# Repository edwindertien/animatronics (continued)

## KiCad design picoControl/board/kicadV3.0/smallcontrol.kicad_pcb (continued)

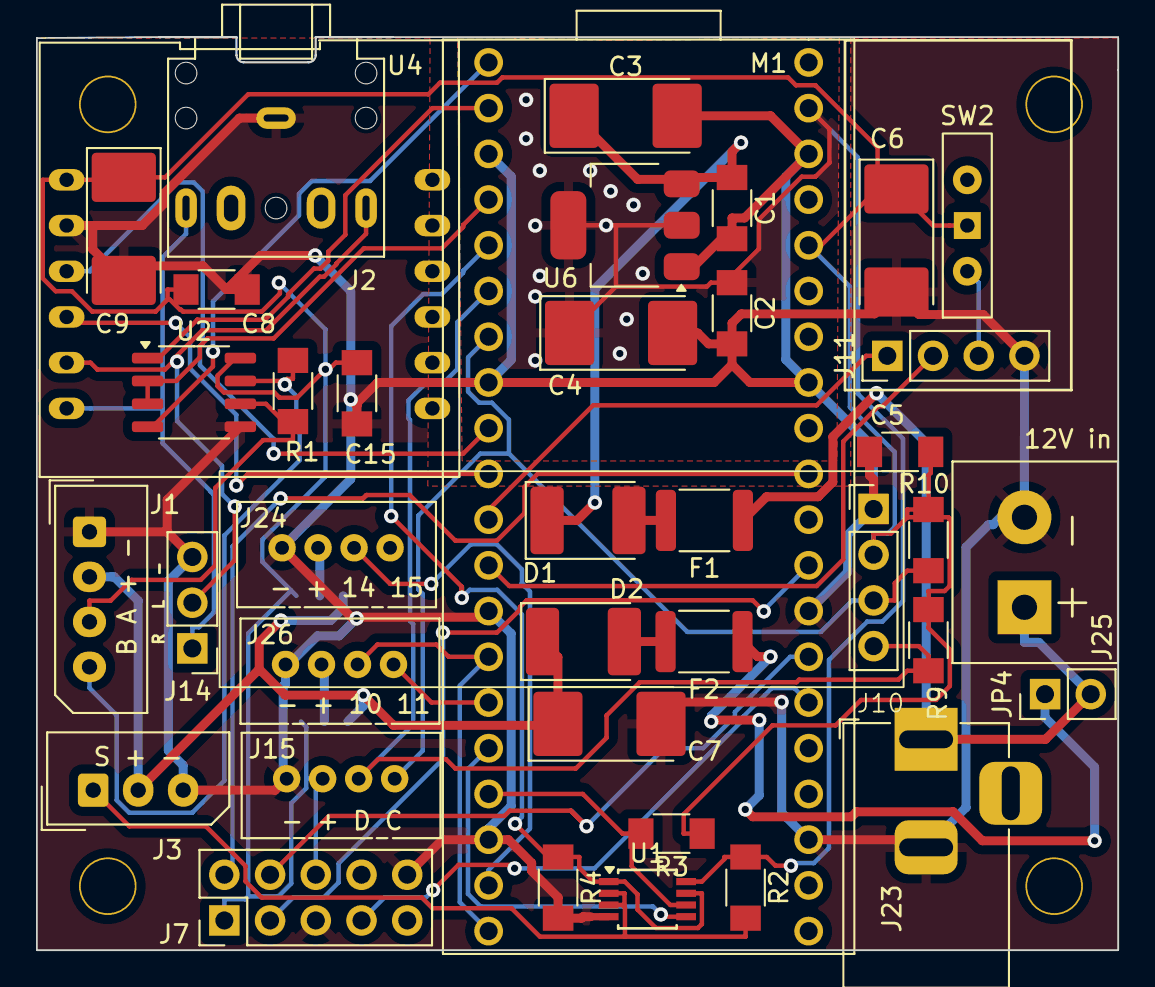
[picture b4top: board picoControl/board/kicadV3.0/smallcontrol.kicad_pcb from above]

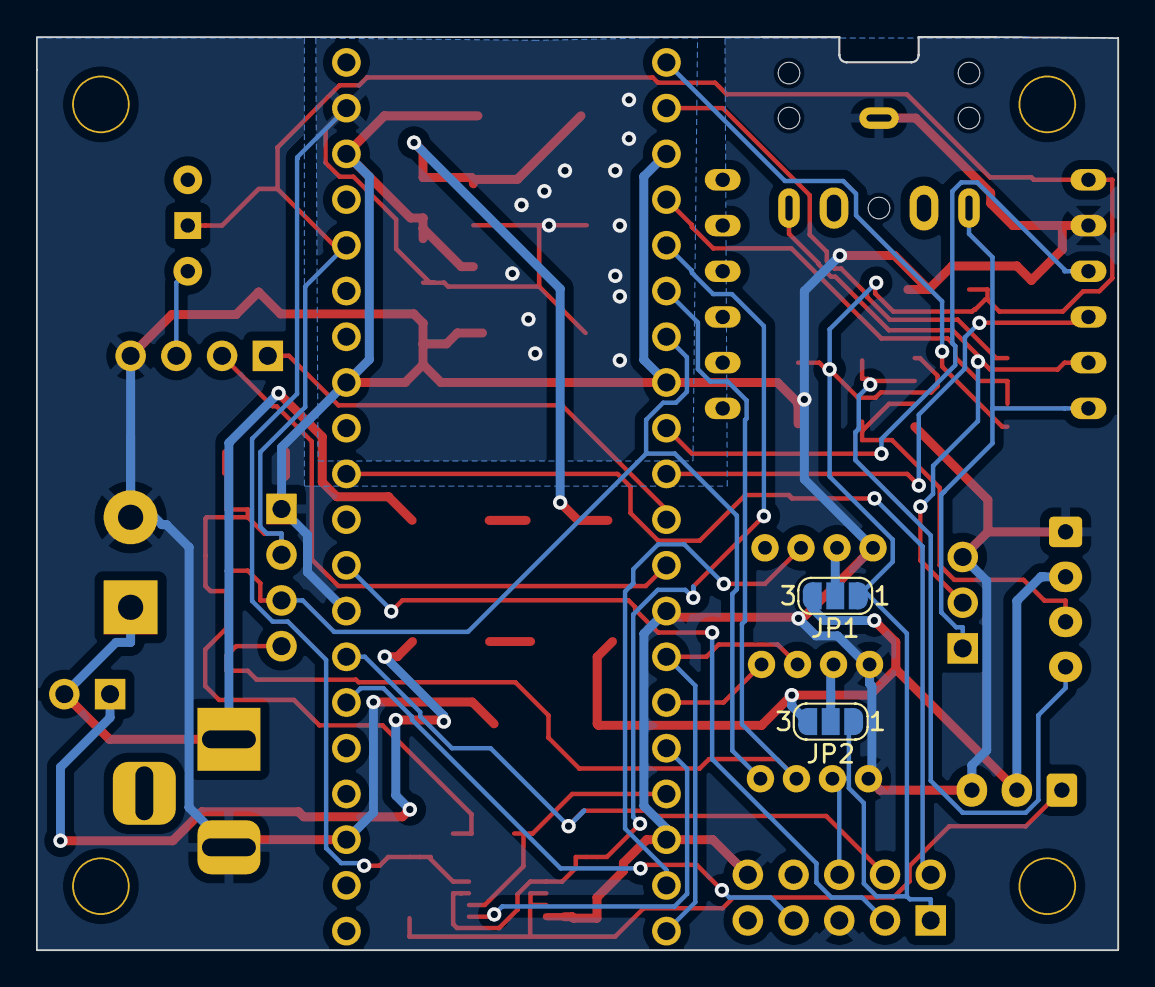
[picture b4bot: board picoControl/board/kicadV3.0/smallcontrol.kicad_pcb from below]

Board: 2 copper layers, 60.1 x 50.7 mm, 45 parts (2 on the bottom side), 36 nets.

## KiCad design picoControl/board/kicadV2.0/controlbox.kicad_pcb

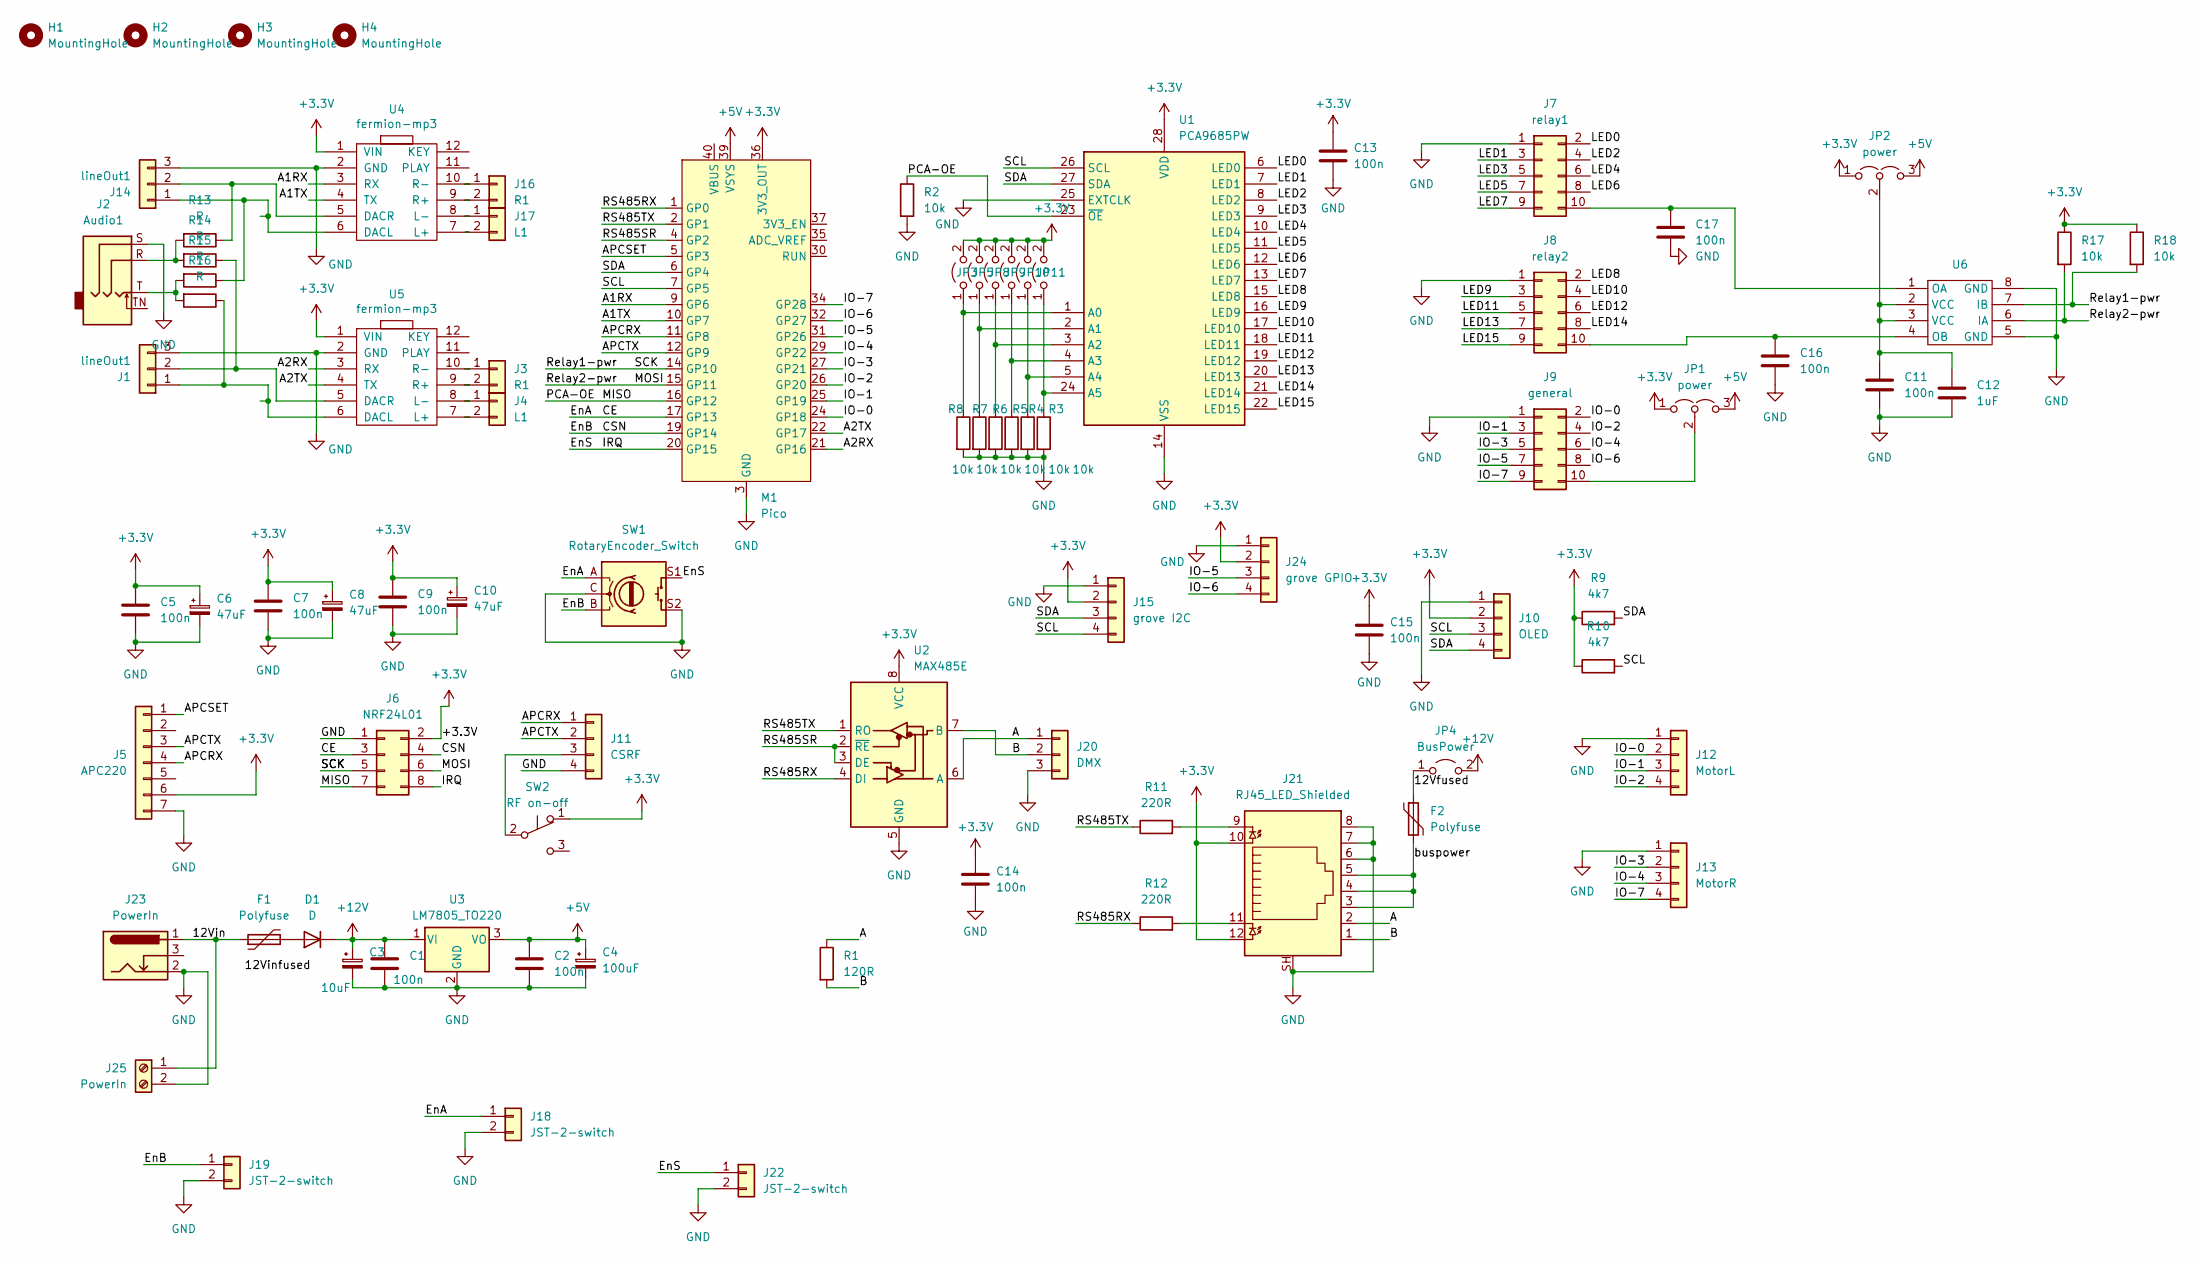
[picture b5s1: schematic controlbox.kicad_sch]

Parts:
C1, C2, C5, C7, C9, C11, C13, C14, C15, C16, C17: 100n; C_1206
C3: 10uF; CP_Elec_D6.3mm_H6.1mm
C4: 100uF; CP_Elec_D6.3mm_H6.1mm
C6, C8, C10: 47uF; CP_Elec_D6.3mm_H6.1mm
C12: 1uF; C_1206
D1: D; D_2512_6332Metric_Pad1.52x3.35mm_HandSolder
F1, F2: Polyfuse; Fuse_2920_7451Metric
H1, H2, H3, H4: MountingHole; MountingHole_3mm
J1, J14: lineOut1; PinHeader_1x03_P2.54mm_Vertical
J2: Audio1; Jack_3.5mm_CUI_SJ1-3525N_Horizontal
J3, J16: R1; JST_XH_B2B-XH-A_1x02_P2.50mm_Vertical
J4, J17: L1; JST_XH_B2B-XH-A_1x02_P2.50mm_Vertical
J5: APC220
J6: NRF24L01; PinHeader_2x04_P2.54mm_Vertical
J7: relay1; IDC-Header_2x05_P2.54mm_Vertical
J8: relay2; IDC-Header_2x05_P2.54mm_Vertical
J9: general; IDC-Header_2x05_P2.54mm_Vertical
J10: OLED; OLED128x32
J11: CSRF; PinHeader_1x04_P2.54mm_Vertical
J12: MotorL; JST_XH_B4B-XH-A_1x04_P2.50mm_Vertical
J13: MotorR; JST_XH_B4B-XH-A_1x04_P2.50mm_Vertical
J15: grove I2C; Grove_1x04
J18, J19, J22: JST-2-switch; JST_XH_B2B-XH-A_1x02_P2.50mm_Vertical
J20: DMX; JST_XH_B3B-XH-A_1x03_P2.50mm_Vertical
J21: RJ45_LED_Shielded; RJ45_Amphenol_RJHSE538X
J23: PowerIn; BarrelJack_Horizontal
J24: grove GPIO; Grove_1x04
J25: PowerIn; TerminalBlock_OnShore_1x02_P5.00mm_Horizontal
JP1, JP2: power; PinHeader_1x03_P2.54mm_Vertical
JP3, JP5, JP8, JP9, JP10, JP11: Jumper_2_Open; SolderJumper-2_P1.3mm_Open_RoundedPad1.0x1.5mm
JP4: BusPower; PinHeader_1x02_P2.54mm_Vertical
M1: Pico; RaspberryPi_PicoW_SocketTHT
R1: 120R; R_1206
R2, R3, R4, R5, R6, R7, R8, R17, R18: 10k; R_1206
R9, R10: 4k7; R_1206
R11, R12: 220R; R_1206
R13, R14, R15, R16: R; R_1206
SW1: RotaryEncoder_Switch; RotaryEncoder_Alps_EC11E-Switch_Vertical_H20mm
SW2: RF on-off; SW_Slide_1P2T_CK_OS102011MS2Q
U1: PCA9685PW; TSSOP-28_4.4x9.7mm_P0.65mm
U2: MAX485E; SO-8_3.9x4.9mm_P1.27mm
U3: LM7805_TO220; TO-220-3_Vertical
U4, U5: fermion-mp3
U6: SO-8_3.9x4.9mm_P1.27mm

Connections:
+3.3V: C5.1, C6.1, C7.1, C8.1, C9.1, C10.1, C13.1, C14.1, C15.1, J5.6, J6.2, J10.2, J15.2, J21.10, J21.12, J24.2, JP1.1 (A), JP2.1 (A), JP3.2 (B), JP5.2 (B), JP8.2 (B), JP9.2 (B), JP10.2 (B), JP11.2 (B), M1.36 (3V3_OUT), R9.1, R10.1, R17.1, R18.1, SW2.1 (A), U1.28 (VDD), U2.8 (VCC), U4.1 (VIN), U5.1 (VIN)
+5V: C2.1, C4.1, JP1.3 (B), JP2.3 (B), M1.39 (VSYS), U3.3 (VO)
+12V: C1.1, C3.1, D1.1 (K), JP4.2 (B), U3.1 (VI)
/12Vfused: F2.1, JP4.1 (A)
/12Vin: F1.1, J23.1, J25.1
/A: J20.1, J21.2, R1.1, U2.6 (A)
/A1RX: M1.9 (GP6), U4.3 (RX)
/A1TX: M1.10 (GP7), U4.4 (TX)
/A2RX: M1.21 (GP16), U5.3 (RX)
/A2TX: M1.22 (GP17), U5.4 (TX)
/APCRX: J5.4, J11.1, M1.11 (GP8)
/APCSET: J5.1, M1.5 (GP3)
/APCTX: J5.3, J11.2, M1.12 (GP9)
/B: J20.2, J21.1, R1.2, U2.7 (B)
/CE: J6.3, J18.1, M1.17 (GP13), SW1.A
/CSN: J6.4, J19.1, M1.19 (GP14), SW1.B
/EnS: J6.8, J22.1, M1.20 (GP15), SW1.S1
/IO-0: J9.2, J12.2, M1.24 (GP18)
/IO-1: J9.3, J12.3, M1.25 (GP19)
/IO-2: J9.4, J12.4, M1.26 (GP20)
/IO-3: J9.5, J13.2, M1.27 (GP21)
/IO-4: J9.6, J13.3, M1.29 (GP22)
/IO-5: J9.7, J24.3, M1.31 (GP26)
/IO-6: J9.8, J24.4, M1.32 (GP27)
/IO-7: J9.9, J13.4, M1.34 (GP28)
/LED0: J7.2, U1.6 (LED0)
/LED1: J7.3, U1.7 (LED1)
/LED2: J7.4, U1.8 (LED2)
/LED3: J7.5, U1.9 (LED3)
/LED4: J7.6, U1.10 (LED4)
/LED5: J7.7, U1.11 (LED5)
/LED6: J7.8, U1.12 (LED6)
/LED7: J7.9, U1.13 (LED7)
/LED8: J8.2, U1.15 (LED8)
/LED9: J8.3, U1.16 (LED9)
/LED10: J8.4, U1.17 (LED10)
/LED11: J8.5, U1.18 (LED11)
/LED12: J8.6, U1.19 (LED12)
/LED13: J8.7, U1.20 (LED13)
/LED14: J8.8, U1.21 (LED14)
/LED15: J8.9, U1.22 (LED15)
/MISO: J6.7, M1.16 (GP12), R2.1, U1.23 (~OE)
/MOSI: J6.6, M1.15 (GP11), R17.2, U6.6 (IA)
/RS485RX: M1.1 (GP0), R12.1, U2.4 (DI)
/RS485SR: M1.4 (GP2), U2.2 (~RE), U2.3 (DE)
/RS485TX: M1.2 (GP1), R11.1, U2.1 (RO)
/Relay1-pwr: J6.5, M1.14 (GP10), R18.2, U6.7 (IB)
/SCL: J10.3, J15.4, M1.7 (GP5), R10.2, U1.26 (SCL)
/SDA: J10.4, J15.3, M1.6 (GP4), R9.2, U1.27 (SDA)
/buspower: F2.2, J21.3, J21.4, J21.5
GND: C1.2, C2.2, C3.2, C4.2, C5.2, C6.2, C7.2, C8.2, C9.2, C10.2, C11.2, C12.2, C13.2, C14.2, C15.2, C16.2, C17.2, J1.3, J2.S, J5.7, J6.1, J7.1, J8.1, J9.1, J10.1, J11.4, J12.1, J13.1, J14.3, J15.1, J18.2, J19.2, J20.3, J21.6, J21.7, J21.8, J21.SH, J22.2, J23.2, J24.1, J25.2, M1.3 (GND), M1.8 (GND), M1.13 (GND), M1.18 (GND), M1.23 (GND), M1.28 (GND), M1.33 (GND), M1.38 (GND), R2.2, R3.2, R4.2, R5.2, R6.2, R7.2, R8.2, SW1.C, SW1.S2, U1.14 (VSS), U1.25 (EXTCLK), U2.5 (GND), U3.2 (GND), U4.2 (GND), U5.2 (GND), U6.5 (GND), U6.8 (GND)
unnamed: D1.2 (A), F1.2
unnamed: J1.1, R16.1, U5.6 (DACL)
unnamed: J1.2, R14.1, U5.5 (DACR)
unnamed: J2.R, R13.2, R14.2
unnamed: J2.T, R15.2, R16.2
unnamed: J3.1, U5.10 (R-)
unnamed: J3.2, U5.9 (R+)
unnamed: J4.1, U5.8 (L-)
unnamed: J4.2, U5.7 (L+)
unnamed: C17.1, J7.10, U6.1 (OA)
unnamed: C16.1, J8.10, U6.4 (OB)
unnamed: J9.10, JP1.2 (C)
unnamed: J11.3, SW2.2 (B)
unnamed: J14.1, R15.1, U4.6 (DACL)
unnamed: J14.2, R13.1, U4.5 (DACR)
unnamed: J16.1, U4.10 (R-)
unnamed: J16.2, U4.9 (R+)
unnamed: J17.1, U4.8 (L-)
unnamed: J17.2, U4.7 (L+)
unnamed: J21.9, R11.2
unnamed: J21.11, R12.2
unnamed: C11.1, C12.1, JP2.2 (C), U6.2 (VCC), U6.3 (VCC)
unnamed: JP3.1 (A), R8.1, U1.1 (A0)
unnamed: JP5.1 (A), R7.1, U1.2 (A1)
unnamed: JP8.1 (A), R6.1, U1.3 (A2)
unnamed: JP9.1 (A), R5.1, U1.4 (A3)
unnamed: JP10.1 (A), R4.1, U1.5 (A4)
unnamed: JP11.1 (A), R3.1, U1.24 (A5)

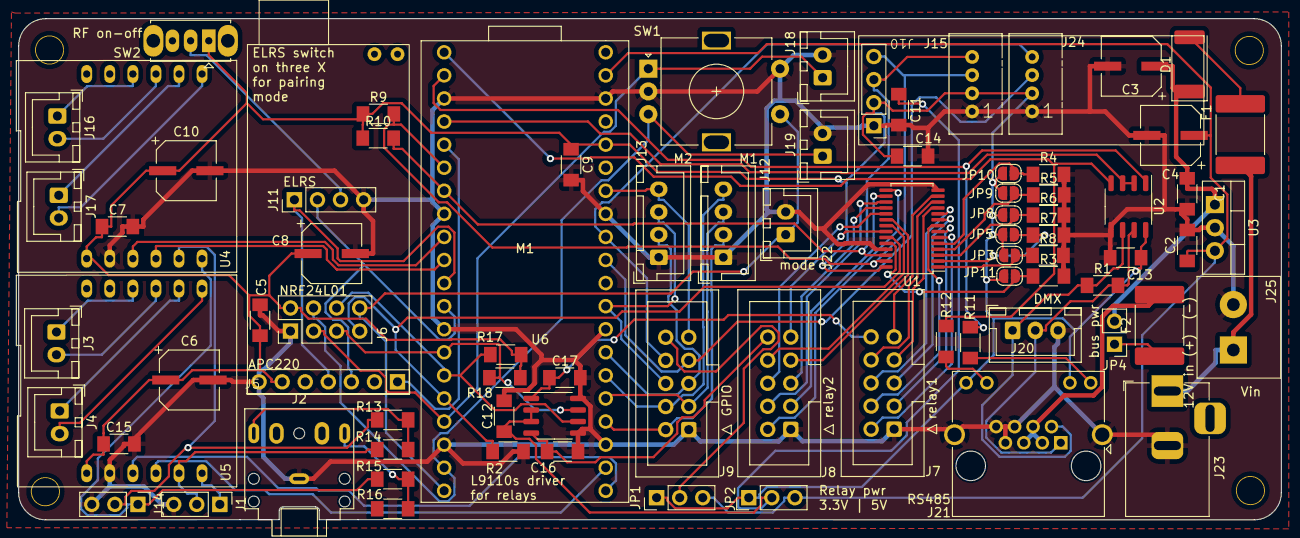
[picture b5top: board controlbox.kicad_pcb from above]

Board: 2 copper layers, 139.0 x 55.2 mm, 85 parts (0 on the bottom side), 79 nets.

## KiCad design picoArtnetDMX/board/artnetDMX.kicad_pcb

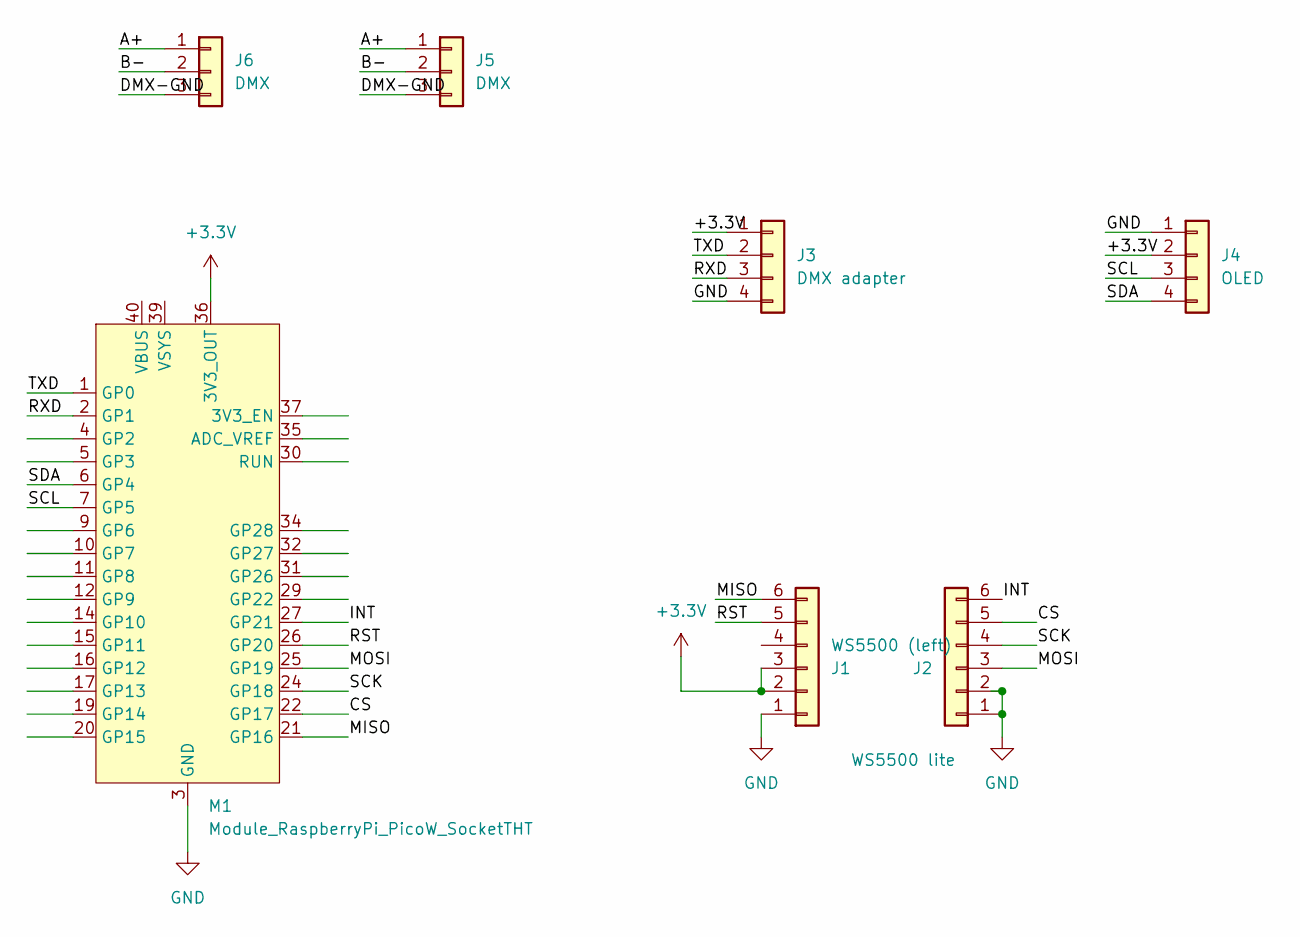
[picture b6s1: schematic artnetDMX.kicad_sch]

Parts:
J1: WS5500 (left); PinSocket_1x06_P2.54mm_Vertical
J2: WS5500 lite; PinSocket_1x06_P2.54mm_Vertical
J3: DMX adapter; PinSocket_1x04_P2.54mm_Vertical
J4: OLED; PinSocket_1x04_P2.54mm_Vertical
J5: DMX; Jack_XLR_Neutrik_NC3FAH_Horizontal
J6: DMX; TE_826576-3_1x03_P3.96mm_Vertical
M1: Module_RaspberryPi_PicoW_SocketTHT; RaspberryPi_PicoW_SocketTHT

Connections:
+3.3V: J1.2, J1.3, J3.1, J4.2, M1.36 (3V3_OUT)
/A+: J5.1, J6.1
/B-: J5.2, J6.2
/CS: J2.5, M1.22 (GP17)
/DMX-GND: J5.3, J6.3
/INT: J2.6, M1.27 (GP21)
/MISO: J1.6, M1.21 (GP16)
/MOSI: J2.3, M1.25 (GP19)
/RST: J1.5, M1.26 (GP20)
/RXD: J3.3, M1.2 (GP1)
/SCK: J2.4, M1.24 (GP18)
/SCL: J4.3, M1.7 (GP5)
/SDA: J4.4, M1.6 (GP4)
/TXD: J3.2, M1.1 (GP0)
GND: J1.1, J2.1, J2.2, J3.4, J4.1, M1.3 (GND), M1.8 (GND), M1.13 (GND), M1.18 (GND), M1.23 (GND), M1.28 (GND), M1.33 (GND), M1.38 (GND)

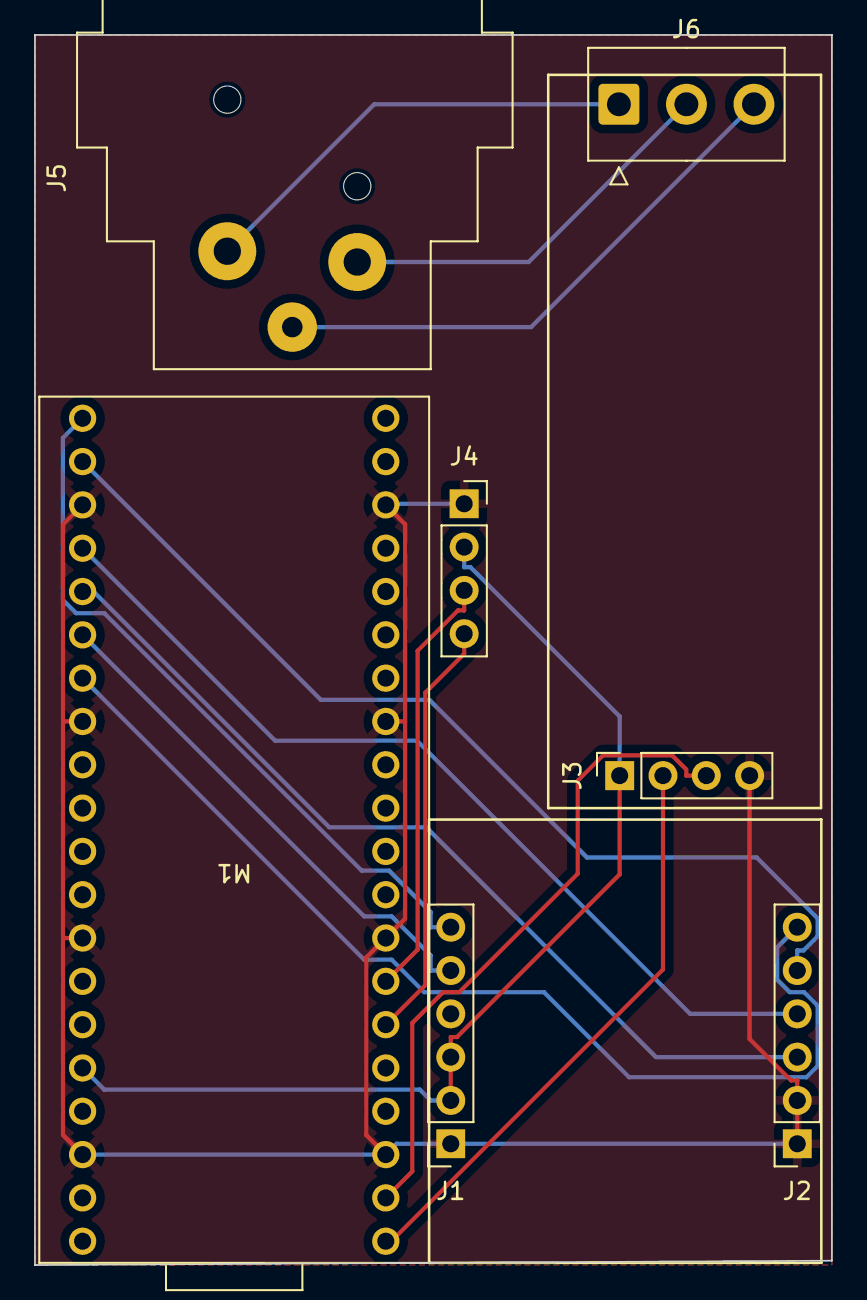
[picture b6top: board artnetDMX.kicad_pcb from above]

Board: 2 copper layers, 46.7 x 72.1 mm, 7 parts (0 on the bottom side), 15 nets.

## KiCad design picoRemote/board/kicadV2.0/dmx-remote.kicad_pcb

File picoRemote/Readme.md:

# PicoRemote — Universal RC Transmitter

A multi-vehicle RC transmitter built on the Raspberry Pi Pico (RP2040) using the earlephilhower Arduino core. Communicates over ELRS 4.x via CRSF at 420000 baud, with bidirectional telemetry. One codebase covers all vehicles — select the target in `config.h`.

---

## Hardware

### PCB V2.0

| Item | Detail |
|------|--------|
| MCU | Raspberry Pi Pico (RP2040) |
| RF module | BetaFPV MicroTX 2.4 GHz 1W, ELRS 4.0.0 firmware |
| ELRS settings | 333 Hz packet rate, 16ch/2 switch mode, telemetry 1:128 |
| UART | Serial1 — GP0 TX → module, GP1 RX ← module |
| Telemetry loopback | 1 kΩ resistor between GP0 and GP1 (half-duplex loopback) |
| Mux | 16-channel analog multiplexer on A0, address pins GP16–GP19 |
| Display | SSD1306 128×32 OLED on I2C1 (SCL=GP7, SDA=GP6) |
| Nunchuck | Wii Nunchuck on I2C0 |
| Keypad | 12-button matrix, columns GP2/3/11, rows GP12/13/14/15 |
| Battery gauge | MAX17048 on I2C1 |
| Solder jumper | PCB V2.0 — must be closed to bypass TX buffer for telemetry RX |

### Critical hardware notes

**1 kΩ resistor between GP0 and GP1** — required for telemetry reception. The ELRS module sends telemetry frames back during the inter-packet gap (~3ms at 333Hz). The resistor creates a half-duplex loopback so the RP2040 RX pin sees these frames. Without it, RSSI and LQ are never received and the OLED signal bars always show empty.

**ELRS firmware version** — must be **4.0.0 or later** on both microTX and nanoRX. The 16ch/2 switch mode required for full channel count was introduced in ELRS 3.4.3. Do not downgrade.

**Solder jumper (PCB V2.0)** — a small solder jumper on the bottom of the PCB must be closed to bypass the TX buffer and allow the telemetry loopback to work.

**Grove I2C connector** — SCL and SDA are swapped relative to the OLED connector.

**Servo cable colour** — counter-intuitive wiring on the 3-axis joystick:
- black = signal, white = GND, red = VCC

Standard servo cables on mux channels:
- brown = GND, red = VCC, orange = signal

**Pull-up/pull-down resistors** — every mux channel has 10k pull-up/pull-down resistors in 8×4 channel SIL arrays on the PCB.

### SPDT switch wiring (voltage divider)

Each 3-position switch uses a voltage divider to produce three analogue levels on one mux channel:

```
3.3V ── R1 ── mux input ── R2 ── GND
                  │
              SPDT centre
```

Software thresholds: `< 64` = low, `64–191` = mid, `> 191` = high.
A 2-position toggle produces only low and high. A potentiometer sweeps through all three zones.

---

## Software structure

```
include/
  config.h          — vehicle selection and per-vehicle hardware config
  crsf.h            — CRSF protocol, telemetry structs, TX/RX API
  crsf_channels.h   — SHARED channel protocol (must be identical on receiver)
  muxcontrol.h      — 16-channel mux driver
  nunchuck.h        — Wii Nunchuck I2C driver
  keypad.h          — 12-button keypad driver
  apcrf.h           — Legacy APC220 RF driver (alternative to CRSF)

src/
  main.cpp          — setup/loop, sampling, CRSF packing, OLED display
  crsf.cpp          — CRSF packet TX, telemetry RX parser
  muxcontrol.cpp    — mux channel read
  keypad.cpp        — keypad scan (returns 12-bit bitmask)
  apcrf.cpp         — legacy RF
```

---

## Vehicle selection

Edit `config.h` and enable exactly one vehicle `#define`:

```c
//#define ANIMAL_LOVE
//#define AMI
#define SCUBA
//#define LUMI
//#define ANIMALTRONIEK_VIS
//#define ANIMALTRONIEK_KREEFT
//#define EXPERIMENTAL
```

Each vehicle block defines:

| Define | Meaning |
|--------|---------|
| `AXIS_X1_SRC` | `channels[]` index for primary X axis |
| `AXIS_Y1_SRC` | `channels[]` index for primary Y axis |
| `AXIS_X2_SRC` | Secondary X (or `AXIS_NOT_CONNECTED` = 255) |
| `AXIS_Y2_SRC` | Secondary Y |
| `ANALOG1_SRC` | Volume pot mux channel index |
| `ARM_MUX_CHANNEL` | Mux channel used as ELRS arm signal |
| `usedChannel[]` | Which mux channels to read (1=read, 0=return 0) |
| `switchChannel[]` | 0=analog, 1=single-throw, 2=SPDT 3-position |
| `invertChannel[]` | 1=invert the mux reading (255-val) |

### Internal `channels[]` array (32 entries)

| Index | Content |
|-------|---------|
| 0–15 | Mux analog reads (0–255) |
| 16 | Nunchuck X axis |
| 17 | Nunchuck Y axis |
| 18 | Nunchuck buttons (`chuck.buttons * 64`: Z=64, C=128, both=192) |
| 19 | Keypad bitmask low byte (bits 0–7) |
| 20 | Switch bank A — mux ch 0–3 packed |
| 21 | Switch bank B — mux ch 4–7 packed |
| 22 | Switch bank C — mux ch 8–11 packed |
| 23 | Switch bank D — mux ch 12–15 packed |
| 24 | Encoder position (LUMI only) |
| 25 | Keypad bitmask high nibble (bits 8–11) |
| 26–31 | Spare |

---

## CRSF channel protocol

Defined in `include/crsf_channels.h` — **copy this file verbatim to the receiver**.

All 16 values are transmitted as 0–255 mapped to CRSF range 172–1811.

| CRSF CH | Index | Content | Notes |
|---------|-------|---------|-------|
| CH1 | 0 | Primary X axis | Nunchuck X / joystick 1X / BetaFPV CH1 |
| CH2 | 1 | Primary Y axis | Nunchuck Y / joystick 1Y / BetaFPV CH2 |
| CH3 | 2 | Secondary X | Joystick 2X / BetaFPV CH3 / 127 if unused |
| CH4 | 3 | Secondary Y | Joystick 2Y / BetaFPV CH4 / 127 if unused |
| CH5 | 4 | ARM | MIN=disarmed, MAX=armed. Driven by `ARM_MUX_CHANNEL`. |
| CH6 | 5 | Analog aux 1 | Volume pot (`ANALOG1_SRC`) |
| CH7 | 6 | Analog aux 2 | Spare |
| CH8 | 7 | Analog aux 3 | Spare |
| CH9 | 8 | Nunchuck buttons | 0=none, 64=Z, 128=C, 192=both |
| CH10 | 9 | Keypad bits 0–7 | Low byte of 12-bit bitmask |
| CH11 | 10 | Keypad bits 8–11 | High nibble (upper 4 bits = 0) |
| CH12 | 11 | Switch bank A | Mux ch 0–3, 2 bits each |
| CH13 | 12 | Switch bank B | Mux ch 4–7, 2 bits each |
| CH14 | 13 | Switch bank C | Mux ch 8–11, 2 bits each |
| CH15 | 14 | Switch bank D | Mux ch 12–15, 2 bits each |
| CH16 | 15 | Spare | Always mid |

### Switch bank encoding

For mux channel N: byte index = `N/4`, bit offset = `(N%4)*2`.
Values: `0b00`=mid, `0b01`=low, `0b10`=high.

```c
uint8_t sw[4] = {
    channels[CRSF_CH_SW_MUX_0_3],  channels[CRSF_CH_SW_MUX_4_7],
    channels[CRSF_CH_SW_MUX_8_11], channels[CRSF_CH_SW_MUX_12_15]
};
if (SWITCH_HIGH(sw, 3))  { /* mux ch 3 HIGH */ }
if (SWITCH_MID(sw, 7))   { /* mux ch 7 MID  */ }
if (SWITCH_LOW(sw, 12))  { /* mux ch 12 LOW */ }
```

### Keypad bitmask

12 keys, one bit each. Multiple simultaneous presses fully supported.

```
Bit: 0  1  2  3  4  5  6  7  8  9  10  11
Key: 1  4  7  *  2  5  8  0  3  6   9   #
```

```c
uint16_t keys = KEYPAD_BITMASK(channels[CRSF_CH_KEYPAD_LO], channels[CRSF_CH_KEYPAD_HI]);
if (KEYPAD_PRESSED(channels[CRSF_CH_KEYPAD_LO], channels[CRSF_CH_KEYPAD_HI], 0)) // '1'
```

### BetaFPV compatibility

CH1–CH4 always carry the primary analog axes, so a standard BetaFPV transmitter can drive any picoControl vehicle without code changes.

---

## Telemetry

**LINK_STATISTICS (0x14)** — `crsfLink`:

| Field | Type | Meaning |
|-------|------|---------|
| `rssi_ant1` | `int8_t` | Uplink RSSI dBm, signed (e.g. −60). Do not negate. |
| `rssi_ant2` | `int8_t` | Second antenna RSSI |
| `link_quality` | `uint8_t` | Uplink LQ 0–100% |
| `snr` | `int8_t` | Uplink SNR dB |
| `downlink_rssi` | `int8_t` | Ground→air RSSI |
| `downlink_lq` | `uint8_t` | Downlink LQ % |

**BATTERY_SENSOR (0x08)** — `crsfBattery`:

| Field | Type | Meaning |
|-------|------|---------|
| `voltage` | `float` | Pack voltage (V) |
| `current` | `float` | Current (A) |
| `capacity_used` | `uint32_t` | mAh consumed |
| `percent` | `uint8_t` | Remaining % |

Diagnostic counters: `crsfRxBytes`, `crsfFramesOk`, `crsfFramesBadCrc`.

---

## OLED display (128×32)

```
x=  0    21  24      44      65   84              127
y=0 [NAME    ][🔋 xx%     ][LQ:xx%              ]
y=9 [J1◎  ][z][J2◎   ][ sw 4×4 ][ kp 3×4 ][ ▂▄▆ dBm]
y=24                                          [ v ▓░░ ]
```

| Zone | Content |
|------|---------|
| x=0, y=0 | Vehicle name |
| x=38, y=0 | Battery % |
| x=84, y=0 | LQ:xx% |
| J1 cx=10,cy=19,r=9 | Primary joystick (Y inverted for nunchuck) |
| x=21, y=13/19 | Nunchuck C/Z dots |
| J2 cx=34,cy=19,r=9 | Secondary joystick (crosshair only if unconnected) |
| x=44, y=11 | 4×4 switch grid: dot=low, open=mid, filled=high |
| x=65, y=11 | 3×4 keypad grid: dot=up, filled=pressed |
| x=84, y=9–15 | Signal bars + dBm |
| x=84, y=24 | Volume bar |

---

## Debug defines

| Define | Effect |
|--------|--------|
| `DEBUG` | Serial print all channel values at 20Hz |
| `DEBUG_MUX` | Serial print all 16 raw mux reads at 20Hz |

---

## Building

```ini
platform = https://github.com/maxgerhardt/platform-raspberrypi.git
board = pico
board_build.core = earlephilhower
framework = arduino
lib_deps =
    adafruit/Adafruit SSD1306@^2.5.11
    adafruit/Adafruit GFX Library@^1.11.10
    adafruit/Adafruit MAX1704X@^1.0.3
```

---

## Adding a new vehicle

1. Add `#ifdef MYVEHICLE` block in `config.h`
2. Define axis sources, `ANALOG1_SRC`, `ARM_MUX_CHANNEL`, `usedChannel[]`, `switchChannel[]`, `invertChannel[]`
3. Add vehicle name to `processScreen()` in `main.cpp`
4. Add matching `#ifdef MYVEHICLE` block in picoControl's `config.h`

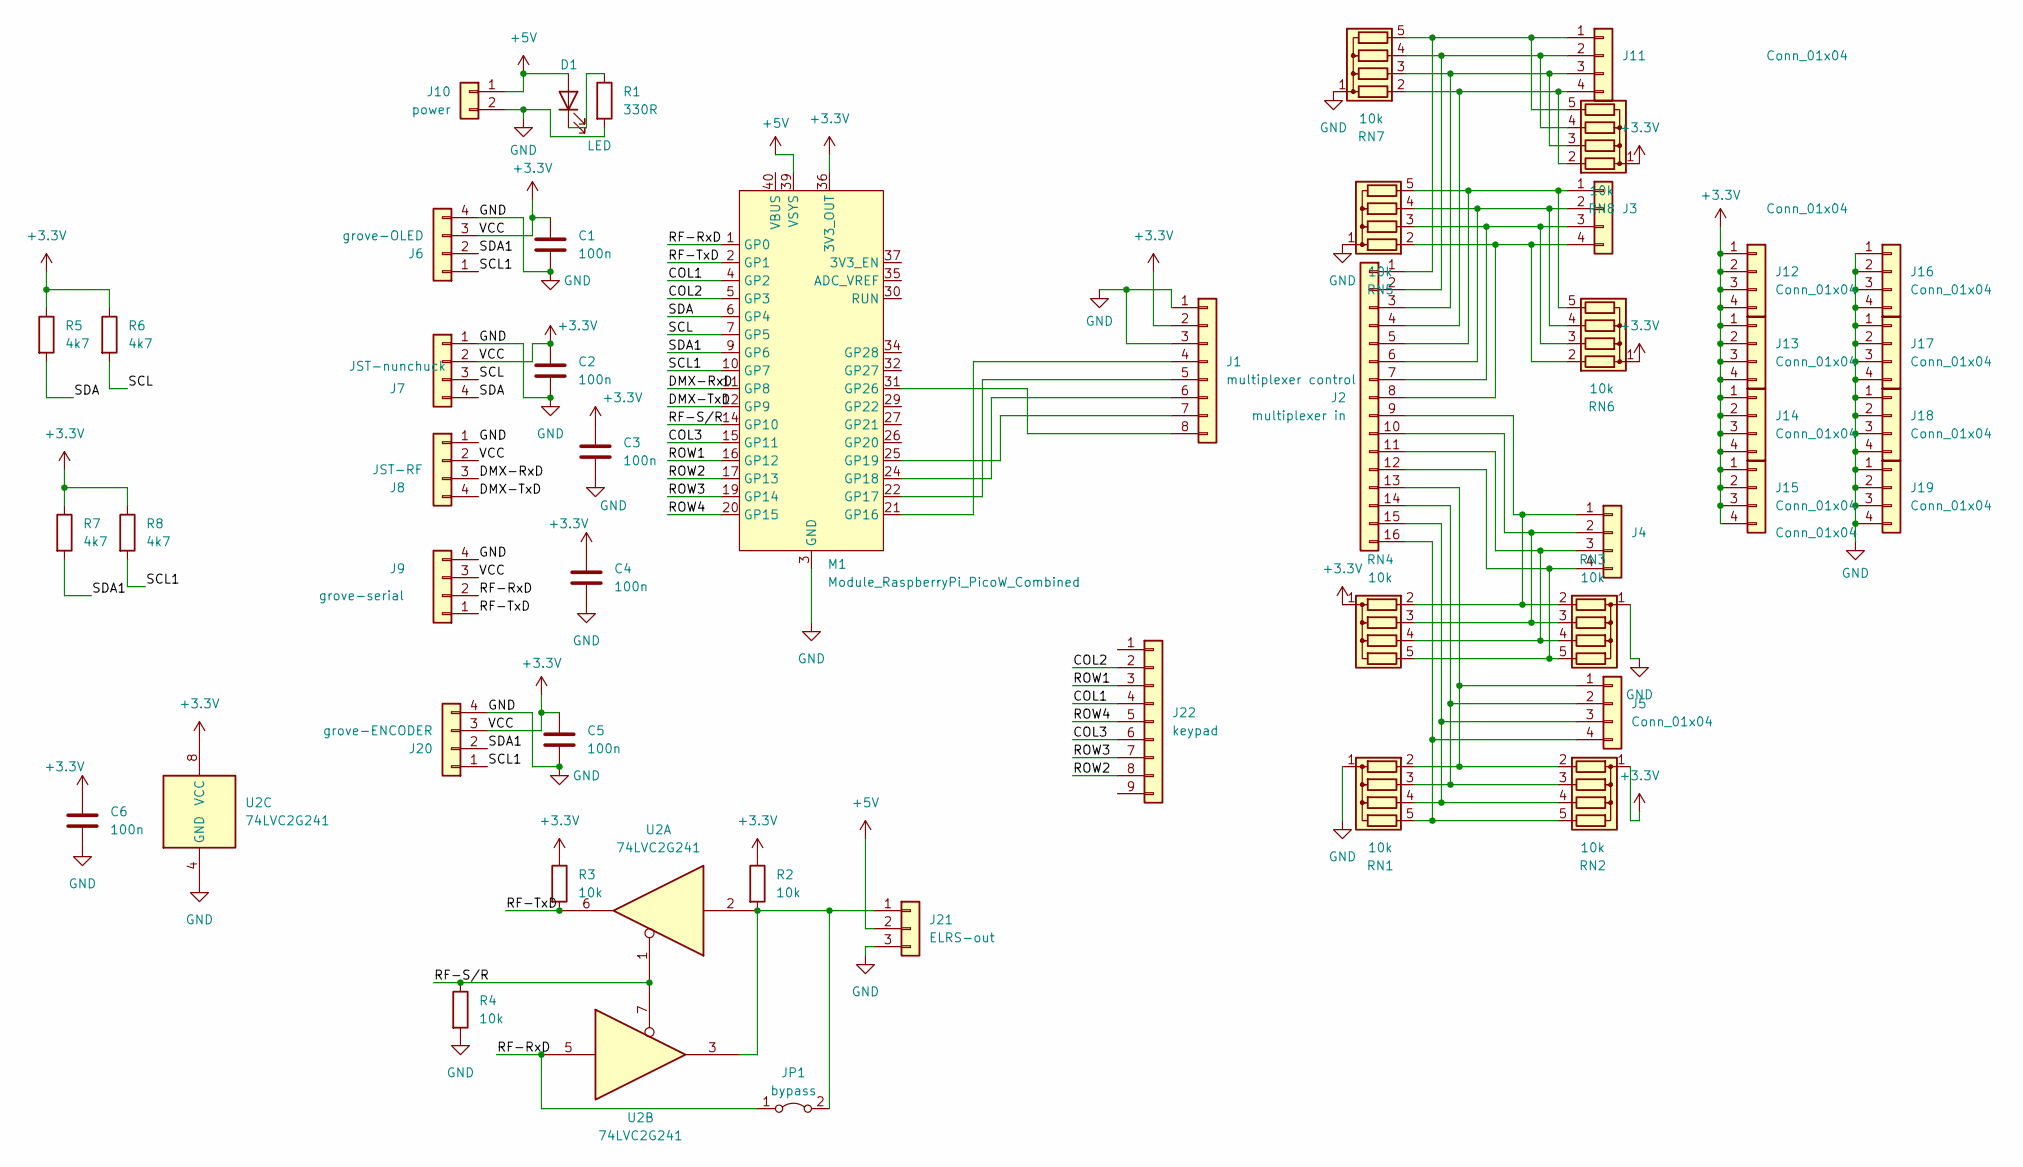
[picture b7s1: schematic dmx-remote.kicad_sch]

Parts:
C1, C2, C3, C4, C5, C6: 100n; C_1206
D1: LED; LED_1206
J1: multiplexer control; PinHeader_1x08_P2.54mm_Vertical
J2: multiplexer in; PinHeader_1x16_P2.54mm_Vertical
J3, J4, J5, J11, J12, J13, J14, J15, J16, J17, J18, J19: Conn_01x04; PinHeader_1x04_P2.54mm_Vertical
J6: grove-OLED; NS-Tech_Grove_1x04_P2mm_Vertical
J7: JST-nunchuck; JST_XH_B4B-XH-A_1x04_P2.50mm_Vertical
J8: JST-RF; JST_XH_B4B-XH-A_1x04_P2.50mm_Vertical
J9: grove-serial; NS-Tech_Grove_1x04_P2mm_Vertical
J10: power; JST_XH_B2B-XH-A_1x02_P2.50mm_Vertical
J20: grove-ENCODER; NS-Tech_Grove_1x04_P2mm_Vertical
J21: ELRS-out; PinHeader_1x03_P2.54mm_Vertical
J22: keypad; PinHeader_1x09_P2.54mm_Vertical
JP1: bypass; SolderJumper-2_P1.3mm_Open_Pad1.0x1.5mm
M1: Module_RaspberryPi_PicoW_Combined; RaspberryPi_PicoW_SocketTHT
R1: 330R; R_1206
R2, R3, R4: 10k; R_1206
R5, R6, R7, R8: 4k7; R_1206
RN1, RN2, RN3, RN4, RN5, RN6, RN7, RN8: 10k; R_Array_SIP5
U2: 74LVC2G241; SSOP-8_3.9x5.05mm_P1.27mm

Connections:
+3.3V: C1.1, C2.1, C3.1, C4.1, C5.1, C6.1, J1.2, J6.3, J7.2, J8.2, J9.3, J12.1, J12.2, J12.3, J12.4, J13.1, J13.2, J13.3, J13.4, J14.1, J14.2, J14.3, J14.4, J15.1, J15.2, J15.3, J15.4, J20.3, M1.36 (3V3_OUT), R2.1, R3.1, R5.1, R6.1, R7.1, R8.1, RN2.1 (common), RN4.1 (common), RN6.1 (common), RN8.1 (common), U2.8 (VCC)
+5V: D1.2 (A), J10.1, J21.2, M1.39 (VSYS)
/COL1: J22.4, M1.4 (GP2)
/COL2: J22.2, M1.5 (GP3)
/COL3: J22.6, M1.15 (GP11)
/DMX-RxD: J8.3, M1.11 (GP8)
/DMX-TxD: J8.4, M1.12 (GP9)
/RF-RxD: J9.2, JP1.1 (A), M1.1 (GP0), U2.5
/RF-S/R: M1.14 (GP10), R4.1, U2.1, U2.7
/RF-TxD: J9.1, M1.2 (GP1), R3.2, U2.6
/ROW1: J22.3, M1.16 (GP12)
/ROW2: J22.8, M1.17 (GP13)
/ROW3: J22.7, M1.19 (GP14)
/ROW4: J22.5, M1.20 (GP15)
/SCL: J7.3, M1.7 (GP5), R6.2
/SCL1: J6.1, J20.1, M1.10 (GP7), R8.2
/SDA: J7.4, M1.6 (GP4), R5.2
/SDA1: J6.2, J20.2, M1.9 (GP6), R7.2
GND: C1.2, C2.2, C3.2, C4.2, C5.2, C6.2, J1.1, J1.3, J6.4, J7.1, J8.1, J9.4, J10.2, J16.1, J16.2, J16.3, J16.4, J17.1, J17.2, J17.3, J17.4, J18.1, J18.2, J18.3, J18.4, J19.1, J19.2, J19.3, J19.4, J20.4, J21.3, M1.3 (GND), M1.8 (GND), M1.13 (GND), M1.18 (GND), M1.23 (GND), M1.28 (GND), M1.33 (GND), M1.38 (GND), R1.2, R4.2, RN1.1 (common), RN3.1 (common), RN5.1 (common), RN7.1 (common), U2.4 (GND)
unnamed: D1.1 (K), R1.1
unnamed: J1.4, M1.21 (GP16)
unnamed: J1.5, M1.22 (GP17)
unnamed: J1.6, M1.24 (GP18)
unnamed: J1.7, M1.25 (GP19)
unnamed: J1.8, M1.31 (GP26)
unnamed: J2.5, J3.1, RN5.5 (R4), RN6.5 (R4)
unnamed: J2.6, J3.2, RN5.4 (R3), RN6.4 (R3)
unnamed: J2.7, J3.3, RN5.3 (R2), RN6.3 (R2)
unnamed: J2.8, J3.4, RN5.2 (R1), RN6.2 (R1)
unnamed: J2.9, J4.1, RN3.2 (R1), RN4.2 (R1)
unnamed: J2.10, J4.2, RN3.3 (R2), RN4.3 (R2)
unnamed: J2.11, J4.3, RN3.4 (R3), RN4.4 (R3)
unnamed: J2.12, J4.4, RN3.5 (R4), RN4.5 (R4)
unnamed: J2.13, J5.1, RN1.2 (R1), RN2.2 (R1)
unnamed: J2.14, J5.2, RN1.3 (R2), RN2.3 (R2)
unnamed: J2.15, J5.3, RN1.4 (R3), RN2.4 (R3)
unnamed: J2.16, J5.4, RN1.5 (R4), RN2.5 (R4)
unnamed: J2.1, J11.1, RN7.5 (R4), RN8.5 (R4)
unnamed: J2.2, J11.2, RN7.4 (R3), RN8.4 (R3)
unnamed: J2.3, J11.3, RN7.3 (R2), RN8.3 (R2)
unnamed: J2.4, J11.4, RN7.2 (R1), RN8.2 (R1)
unnamed: J21.1, JP1.2 (B), R2.2, U2.2, U2.3

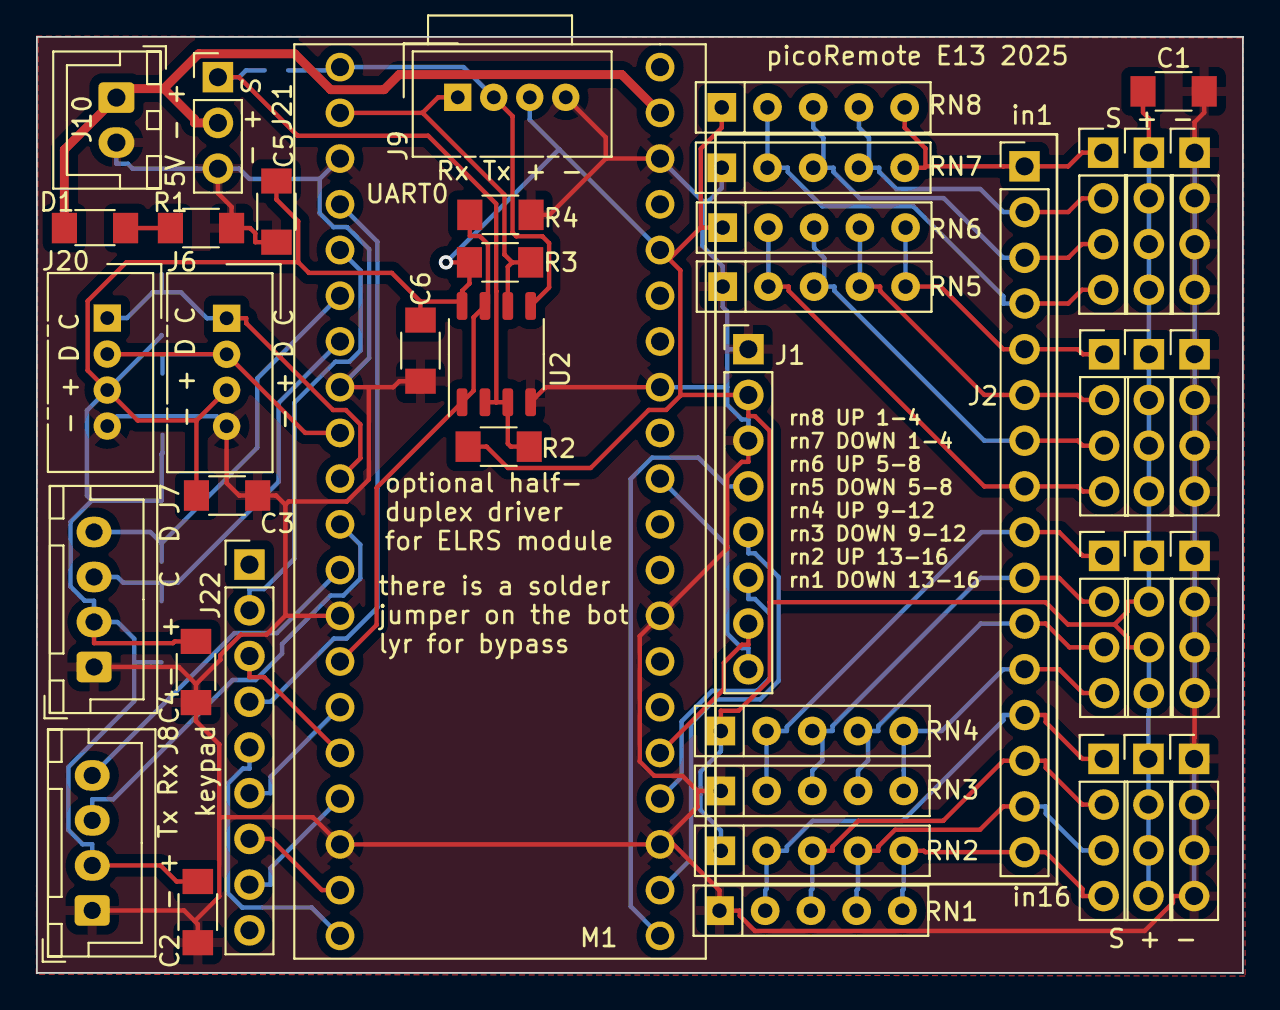
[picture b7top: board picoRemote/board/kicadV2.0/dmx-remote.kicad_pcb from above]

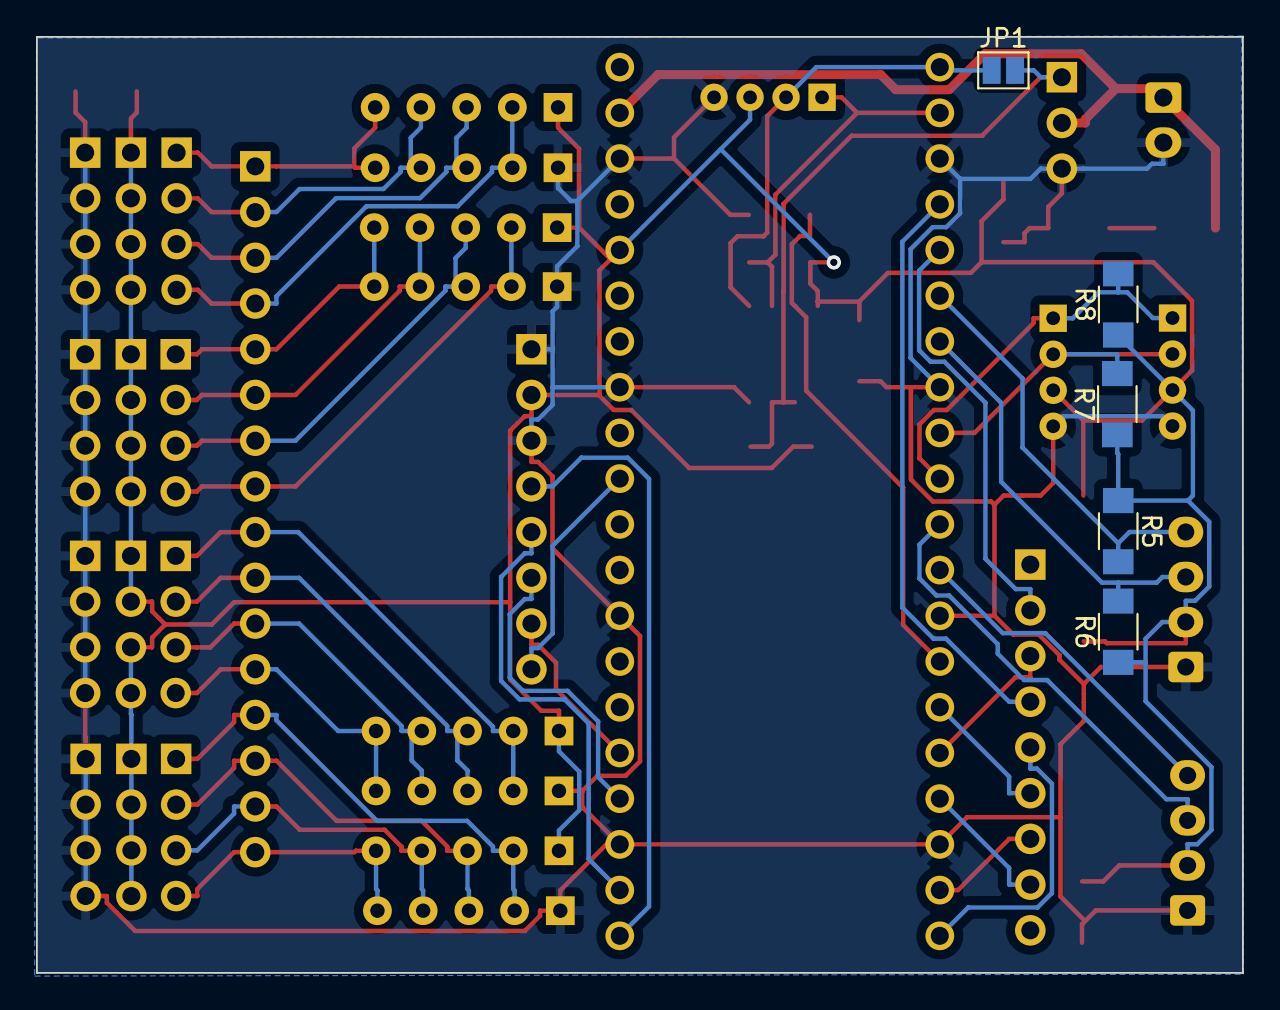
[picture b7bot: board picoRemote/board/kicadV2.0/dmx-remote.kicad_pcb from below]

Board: 2 copper layers, 67.0 x 52.0 mm, 48 parts (5 on the bottom side), 42 nets.
